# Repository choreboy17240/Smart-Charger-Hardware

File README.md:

# Battery On-Board Charger

## Overview

This repository contains the design files for a Battery On-Board Charger, a DC-DC converter
designed to safely charge sealed lead-acid (SLA) batteries from external power sources. The 
system operates as a buck-boost converter with intelligent microcontroller control for charge
management.

Please see the accompanying software repository on GitHub for an example Arduino STM32 
application that can be built under PlatformIO and used to program the on-board STM32 micro
using an ST-Link programmer.  Programming is done using a custom"SWD-Lite" interface that I 
use for compact, low-cost projects.  SWD-Lite uses a standard 1x4 2.54mm male header to 
provide the absolute minimum number of signals needed or the ST-Link programmer to operate.

I'm sharing this design information and the associated software in hopes that others might 
find it interesting or helpful. It's a hobby project for me, so your mileage may vary!

This is my first attempt to share a KiCad (v9.0) project, so I'd be interested to hear
about whether there are issues or not.  I've exported the global custom symbols and footprints
that I used in the design, so hopefully this should be a standalone PWB design.

## Hardware Specifications

#### Battery Charging
- **Input Voltage**: 12-24V DC
- **Output Voltage**: Adjustable (typically 12V-15.5V for lead-acid batteries)
- **Maximum Charge Current**: 500-600mA
- **Controller**: STM32G030K8T6 (64KB Flash, 8KB RAM)
- **Power Stage**: XL6008 DC-DC converter (Buck-Boost topology)
- **Current Sensing**: INA219 I2C sensor
- **Voltage Control**: MCP4726A0 I2C DAC
- **Status Indicator**: RGB LED
- **Interfaces**: UART, I2C, SWD programming port
- **Operating Temperature**: Room temp

#### Battery Undervoltage Protection 
- **Low-Voltage Cutout**: Adjustable limit (trim pot)

## Key Features

- Software-adjustable charge voltage via I2C DAC
- Real-time current and voltage monitoring
- Temperature-compensated charging profiles
- Multi-stage charging (bulk, absorption, float)
- Status indication via RGB LED
- UART interface for diagnostics and monitoring
- Surge and reverse polarity protection
- Thermal management and over-current protection

## Power Conversion Design

The design utilizes an XL6008 DC-DC converter configured in a buck-boost topology:
- Input filtering through hybrid aluminum capacitors
- High-efficiency power inductors (47µH Sunlord MWSA1004S)
- Schottky diode rectification (B360AE)
- High-quality output filtering with polymer capacitors
- Feedback network with DAC-controlled reference voltage

## PCB Design Considerations

- 2-layer PCB with optimized (kinda) thermal design
- Ground plane for noise reduction and thermal dissipation
- Separate analog and digital ground regions
- Thermal management for XL6008 regulator
- EMI/EMC design practices for switching converter
- Power and signal path optimization

## Undervoltage Protection Circuit

The design incorporates a hardware-based undervoltage protection circuit
to prevent battery damage while under load:

- **Components**:
  - LM339 Quad Comparator for voltage threshold detection
  - MMBT3906 PNP transistor (Q1) for relay driver
  - NS_SRS_SPDT relay (K1) for power disconnection
  - Precision resistor divider network for voltage sensing

- **Operation**:
  - Continuously monitors the battery voltage through a resistive divider
  - When battery voltage falls below a preset threshold (adjustable via the
    RV1 trim pot)
  - Comparator triggers, driving the PNP transistor into conduction
  - Relay energizes, disconnecting the load from the battery
  - Hysteresis provided by R11 (1MΩ) prevents oscillation at threshold
  - D4 provides flyback protection for relay coil

- **Benefits**:
  - Prevents deep discharge of batteries
  - Hardware-based protection operates independently of microcontroller
  - Adjustable threshold for different battery types
  - Fast response time for critical undervoltage conditions
  - Failsafe design ensures load disconnection on power loss

The circuit provides essential protection for battery-powered systems, preventing
damage from excessive discharge while allowing normal operation above the safe 
voltage threshold.

**Note:** As battery voltage limits vary across manufacturers and also depend
on how aggressive you want to be in draining the battery, you will need to 
adjust the RV1 trim potentiometer so that the shutoff occurs at the desired 
voltage. Typical range might be around 11.0-11.5 volts, but check the manufacturer's
recommendation for your battery!

## Thermal Performance

The design has been thermally optimized for enclosed operation:
- Maximum regulator temperature: ~52°C (125°F) at 600mA continuous charging
- Thermal steady state reached after ~30 minutes of operation
- Heat-generating components spaced for optimal thermal dissipation
- Current limited to 600mA for reliability in enclosed environments
- Charging current is constrained by the small heat sink are available for the 
  XL6008 converter, driven by the small packaging space availabe in my project.
- Control software limits the maximum current to that range automatically, but
  this is configurable.
- Redesign the PWB to increase the heat sink area or add a glue-on heat sink
  to the XL6008 if you want higher charging current.

## Usage Notes

See the system connection diagram in the `System` folder for details on how
to connect the module for charging and powering a load from the SLA battery.
The DPDT center-off switch allows the user to select between the following
operating modes:
1. `Charge`: Standby mode with the load off and battery being charged
2. `Power`: Active mode with the load on and charger disconnected
3. `Off`: Shuts down the system completely (no charging, no power to load)

The system should nomrally be left in the `Charge` mode, as the smart charger
is designed to charge up the battery and then automatically shift to a 
standby mode for a software configurable period (default is one week) to 
avoid overcharging the battery.

Charging the battery:
1. Switch the DPDT switch to the `Charge`position
2. The charger automatically determines charge state and applies appropriate charging profile
3. RGB LED color and flashing rate indicates charging status:
   - Blue (fast): Fast bulk charging
   - Yellow (medium): Absorption charging
   - Green (slow): Float/maintenance charging
   - Green (short keep-alive pulse every second): Standby mode
4. Once the battery is charged sufficiently, the charger will enter the standby
   state until it's time to top-off the battery.
   
Using the battery to power a load:
1. Switch the DPDT switch to the `Power` position
2. Battery protection circuit will automatically shut-off the load if battery
   voltage drops below the adjustable threshold.

## Software Configuration

The STM32G030 microcontroller requires appropriate firmware to control the charging process:
- Voltage setpoint control via MCP4726A0 DAC
- Current and voltage monitoring via INA219
- Temperature compensation
- Charging state machine
- Safety monitoring

See the companion firmware repository for microcontroller code.

## Limitations

- Maximum continuous charging current limited to 600mA for thermal management
- Not suitable for high-current applications without additional cooling
- Designed for lead-acid batteries (AGM, Gel, Flooded)
- Requires appropriate firmware for operation

## License

MIT open-source license - see the LICENSE file for details.

## Revision History

- 1.0: Initial design released to JLCPCB for prototype boards
- 1.1: Minor updates for silkscreen fixes

## Contact

Email: choreboy17240@gmail.com

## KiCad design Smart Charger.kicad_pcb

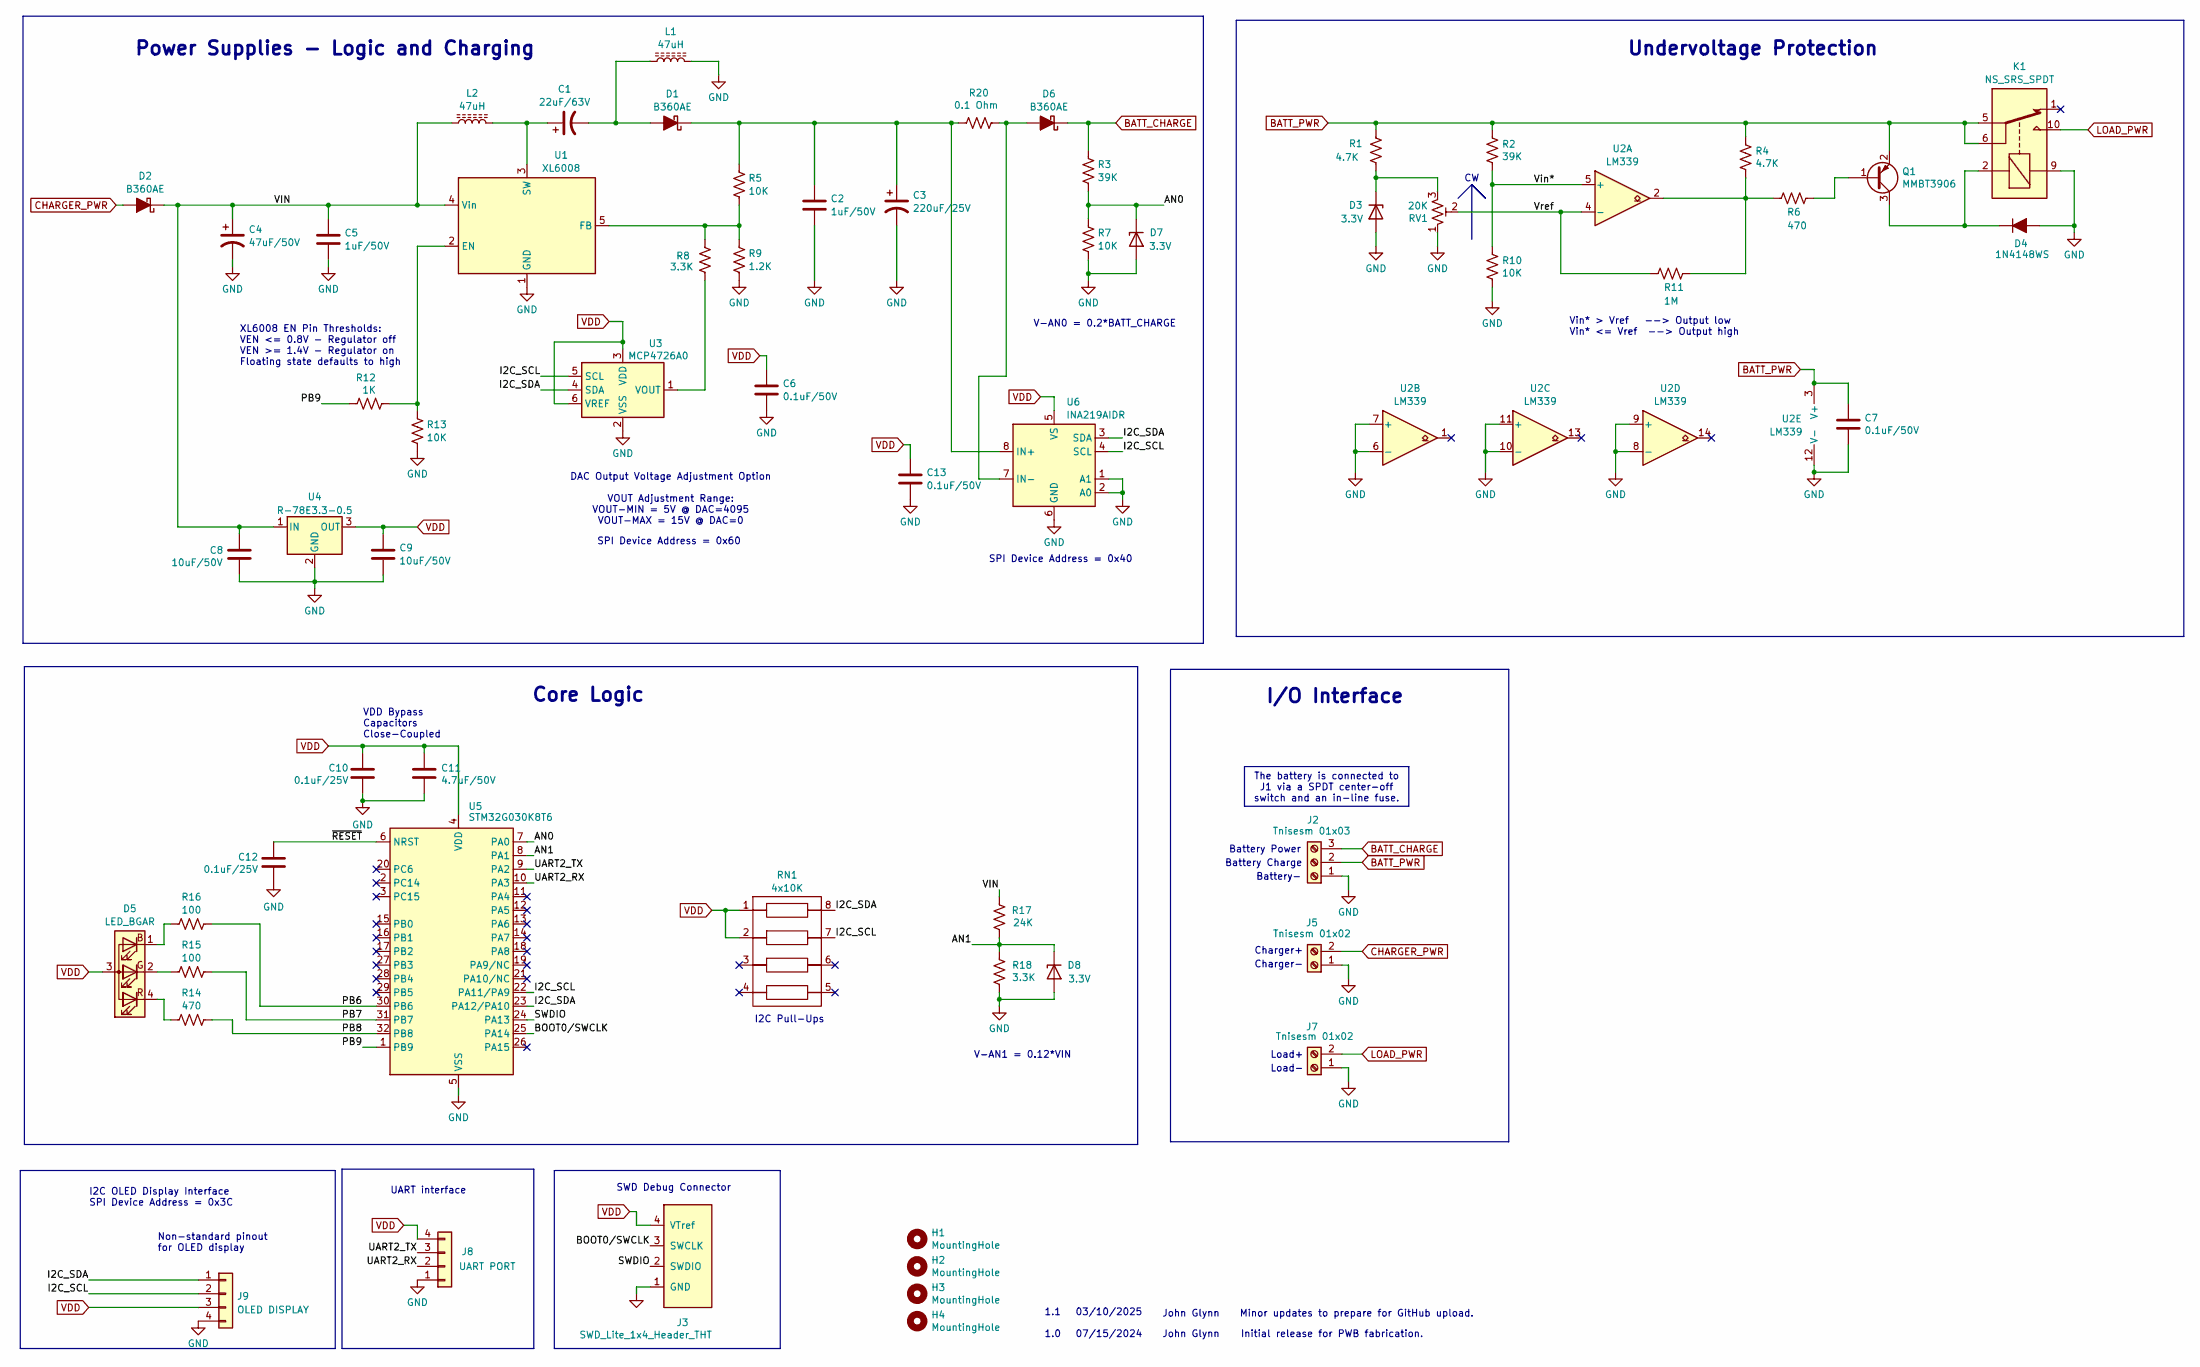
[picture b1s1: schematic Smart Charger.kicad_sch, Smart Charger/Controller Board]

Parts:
C1: 22uF/63V; CP_Elec_6.3x7.7; Mfr P/N HHXB630ARA220MF80G
C2, C5: 1uF/50V; C_1206_3216Metric_Pad1.33x1.80mm_HandSolder; Mfr P/N CL31A105KB9LNNC
C3: 220uF/25V; CP_Radial_D8.0mm_P3.50mm; Mfr P/N APSG250ELL221MHB5S
C4: 47uF/50V; CP_Elec_6.3x7.7; Mfr P/N UUD1H470MCL1GS
C6, C7, C13: 0.1uF/50V; C_0805_2012Metric_Pad1.18x1.45mm_HandSolder; Mfr P/N CC0805KRX7R9BB104
C8, C9: 10uF/50V; C_1206_3216Metric_Pad1.33x1.80mm_HandSolder; Mfr P/N CL31B106KBHNNNE
C10, C12: 0.1uF/25V; C_1206_3216Metric_Pad1.33x1.80mm_HandSolder; Mfr P/N CC1206KRX7R8BB104
C11: 4.7uF/50V; C_1206_3216Metric_Pad1.33x1.80mm_HandSolder; Mfr P/N CL31B475KBHNNNE
D1, D2, D6: B360AE; D_SMA_Handsoldering; Mfr P/N B360AE-13
D3, D7, D8: 3.3V; D_1206_3216Metric_Pad1.42x1.75mm_HandSolder; Mfr P/N MMSZ5226BT1G
D4: 1N4148WS; D_SOD-323_HandSoldering; Mfr P/N 1N4148WS
D5: LED_BGAR; LED_D5.0mm-4_RGB_Staggered_Pins; Mfr P/N N/A
H1, H2, H3, H4: MountingHole; MountingHole_#4-40_Screw
J2: Tnisesm 01x03; TerminalBlock_Tnisesm_Screw_1x03_P5.00mm
J3: SWD_Lite_1x4_Header_THT; PinHeader_1x04_P2.54mm_Vertical
J5, J7: Tnisesm 01x02; TerminalBlock_Tnisesm_Screw_1x02_P5.00mm
J8: UART PORT; PinHeader_1x04_P2.54mm_Vertical
J9: OLED DISPLAY; PinSocket_1x04_P2.54mm_Vertical; Mfr P/N PM254-1-04-Z-8.5
K1: NS_SRS_SPDT; Relay_SPDT_Songle_Miniature_SRS; Mfr P/N SRS-xxVDC-SL
L1, L2: 47uH; L_SMD_Sunlord_MWSA1004S_10.0x11.5mm; Mfr P/N MWSA1004S-470MT
Q1: MMBT3906; SOT-23_Handsolder_Large_Pads; Mfr P/N MMBT3904_R1_00001
R1, R4: 4.7K; R_1206_3216Metric_Pad1.30x1.75mm_HandSolder; Mfr P/N TBD
R2, R3: 39K; R_1206_3216Metric_Pad1.30x1.75mm_HandSolder; Mfr P/N TBD
R5, R7, R10, R13: 10K; R_1206_3216Metric_Pad1.30x1.75mm_HandSolder; Mfr P/N TBD
R6, R14: 470; R_1206_3216Metric_Pad1.30x1.75mm_HandSolder; Mfr P/N TBD
R8, R18: 3.3K; R_1206_3216Metric_Pad1.30x1.75mm_HandSolder; Mfr P/N TBD
R9: 1.2K; R_1206_3216Metric_Pad1.30x1.75mm_HandSolder; Mfr P/N TBD
R11: 1M; R_1206_3216Metric_Pad1.30x1.75mm_HandSolder; Mfr P/N TBD
R12: 1K; R_1206_3216Metric_Pad1.30x1.75mm_HandSolder; Mfr P/N TBD
R15, R16: 100; R_1206_3216Metric_Pad1.30x1.75mm_HandSolder; Mfr P/N TBD
R17: 24K; R_1206_3216Metric_Pad1.30x1.75mm_HandSolder; Mfr P/N TBD
R20: 0.1 Ohm; R_1210_3225Metric_Pad1.30x2.65mm_HandSolder; Mfr P/N TBD
RN1: 4x10K; RN_Array_4x0603; Mfr P/N YC164-FR-0710KL
RV1: 20K; Potentiometer_Bourns_3362P_Vertical; Mfr P/N 3362P-1-223LF
U1: XL6008; TO-252-5L_TabPin3_Hand_Solder; Mfr P/N XL6008E1
U2: LM339; SOIC-14_3.9x8.7mm_P1.27mm; Mfr P/N LM339DR2G
U3: MCP4726A0; SOT-23-6; Mfr P/N MCP4726A0T-E/CH
U4: R-78E3.3-0.5; Converter_DCDC_RECOM_R-78E-0.5_THT
U5: STM32G030K8T6; LQFP-32_7x7mm_P0.8mm; Mfr P/N STM32G030K8T6
U6: INA219AIDR; SOIC-8_3.9x4.9mm_P1.27mm; Mfr P/N INA219AIDR

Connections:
/AN0: D7.1 (K), R3.2, R7.1, U5.7 (PA0)
/AN1: D8.1 (K), R17.2, R18.1, U5.8 (PA1)
/BOOT0/SWCLK: J3.3 (SWCLK), U5.25 (PA14)
/I2C_SCL: J9.2, RN1.7 (R2B), U3.5 (SCL), U5.22 (PA11/PA9), U6.4 (SCL)
/I2C_SDA: J9.1, RN1.8 (R1B), U3.4 (SDA), U5.23 (PA12/PA10), U6.3 (SDA)
/PB6: R16.1, U5.30 (PB6)
/PB7: R15.1, U5.31 (PB7)
/PB8: R14.1, U5.32 (PB8)
/PB9: R12.2, U5.1 (PB9)
/SWDIO: J3.2 (SWDIO), U5.24 (PA13)
/UART2_RX: J8.2, U5.10 (PA3)
/UART2_TX: J8.3, U5.9 (PA2)
/VIN: C4.1, C5.2, C8.1, D2.1 (K), L2.1, R17.1, U1.4 (Vin), U4.1 (IN)
/Vin*: R2.2, R10.1, U2.5 (+)
/Vref: R11.2, RV1.2, U2.4 (-)
/~RESET: C12.1, U5.6 (NRST)
BATT_CHARGE: D6.1 (K), J2.3, R3.1
BATT_PWR: C7.1, J2.2, K1.5, K1.6, Q1.2 (E), R1.1, R2.1, R4.1, U2.3 (V+)
CHARGER_PWR: D2.2 (A), J5.2
GND: C2.1, C3.2, C4.2, C5.1, C6.2, C7.2, C8.2, C9.2, C10.2, C11.2, C12.2, C13.2, D3.2 (A), D4.2 (A), D7.2 (A), D8.2 (A), J2.1, J3.1 (GND), J5.1, J7.1, J8.1, J9.4, K1.9, L1.2, R7.2, R9.2, R10.2, R13.2, R18.2, RV1.1, U1.1 (GND), U2.6 (-), U2.7 (+), U2.8 (-), U2.9 (+), U2.10 (-), U2.11 (+), U2.12 (V-), U3.2 (VSS), U4.2 (GND), U5.5 (VSS), U6.1 (A1), U6.2 (A0), U6.6 (GND)
LOAD_PWR: J7.2, K1.10
unnamed: C1.2, D1.2 (A), L1.1
unnamed: C2.2, C3.1, D1.1 (K), R5.1, R20.2, U6.8 (IN+)
unnamed: D3.1 (K), R1.2, RV1.3
unnamed: D4.1 (K), K1.2, Q1.3 (C)
unnamed: D5.1 (BK), R16.2
unnamed: D5.2 (GK), R15.2
unnamed: D5.4 (RK), R14.2
unnamed: D6.2 (A), R20.1, U6.7 (IN-)
unnamed: Q1.1 (B), R6.1
unnamed: R4.2, R6.2, R11.1, U2.2
unnamed: R12.1, R13.1, U1.2 (EN)
unnamed: R5.2, R8.2, R9.1, U1.5 (FB)
unnamed: C1.1, L2.2, U1.3 (SW)
unnamed: R8.1, U3.1 (VOUT)
VDD: C6.1, C9.1, C10.1, C11.1, C13.1, D5.3 (A), J3.4 (VTref), J8.4, J9.3, RN1.1 (R1A), RN1.2 (R2A), U3.3 (VDD), U3.6 (VREF), U4.3 (OUT), U5.4 (VDD), U6.5 (VS)

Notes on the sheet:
Battery Charge
Battery-
I/O Interface
DAC Output Voltage Adjustment Option VOUT Adjustment Range: VOUT-MIN = 5V @ DAC=4095 VOUT-MAX = 15V @ DAC=0
Battery Power
I2C Pull-Ups
VDD Bypass Capacitors Close-Coupled
Initial release for PWB fabrication.
Minor updates to prepare for GitHub upload.
Charger+
1.0
Power Supplies - Logic and Charging
Non-standard pinout for OLED display
I2C OLED Display Interface SPI Device Address = 0x3C
Load+
SPI Device Address = 0x60
John Glynn
Vin* > Vref --> Output low Vin* <= Vref --> Output high
XL6008 EN Pin Thresholds: VEN <= 0.8V - Regulator off VEN >= 1.4V - Regulator on Floating state defaults to high
03/10/2025
Load-
V-AN1 = 0.12*VIN
UART interface
V-AN0 = 0.2*BATT_CHARGE
Undervoltage Protection
Core Logic
1.1
07/15/2024
Charger-
SPI Device Address = 0x40
SWD Debug Connector
The battery is connected to J1 via a SPDT center-off switch and an in-line fuse.

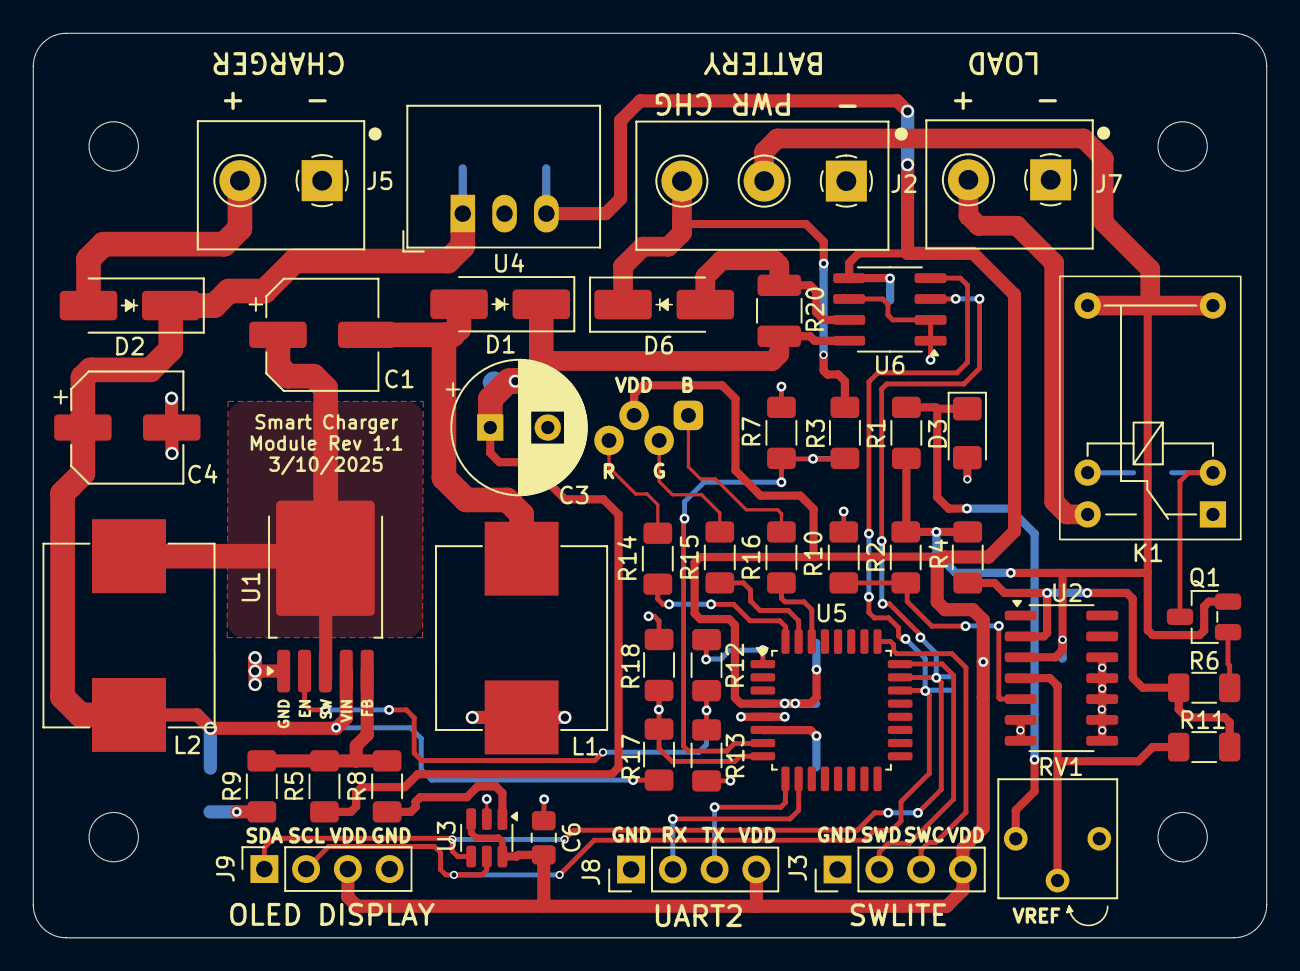
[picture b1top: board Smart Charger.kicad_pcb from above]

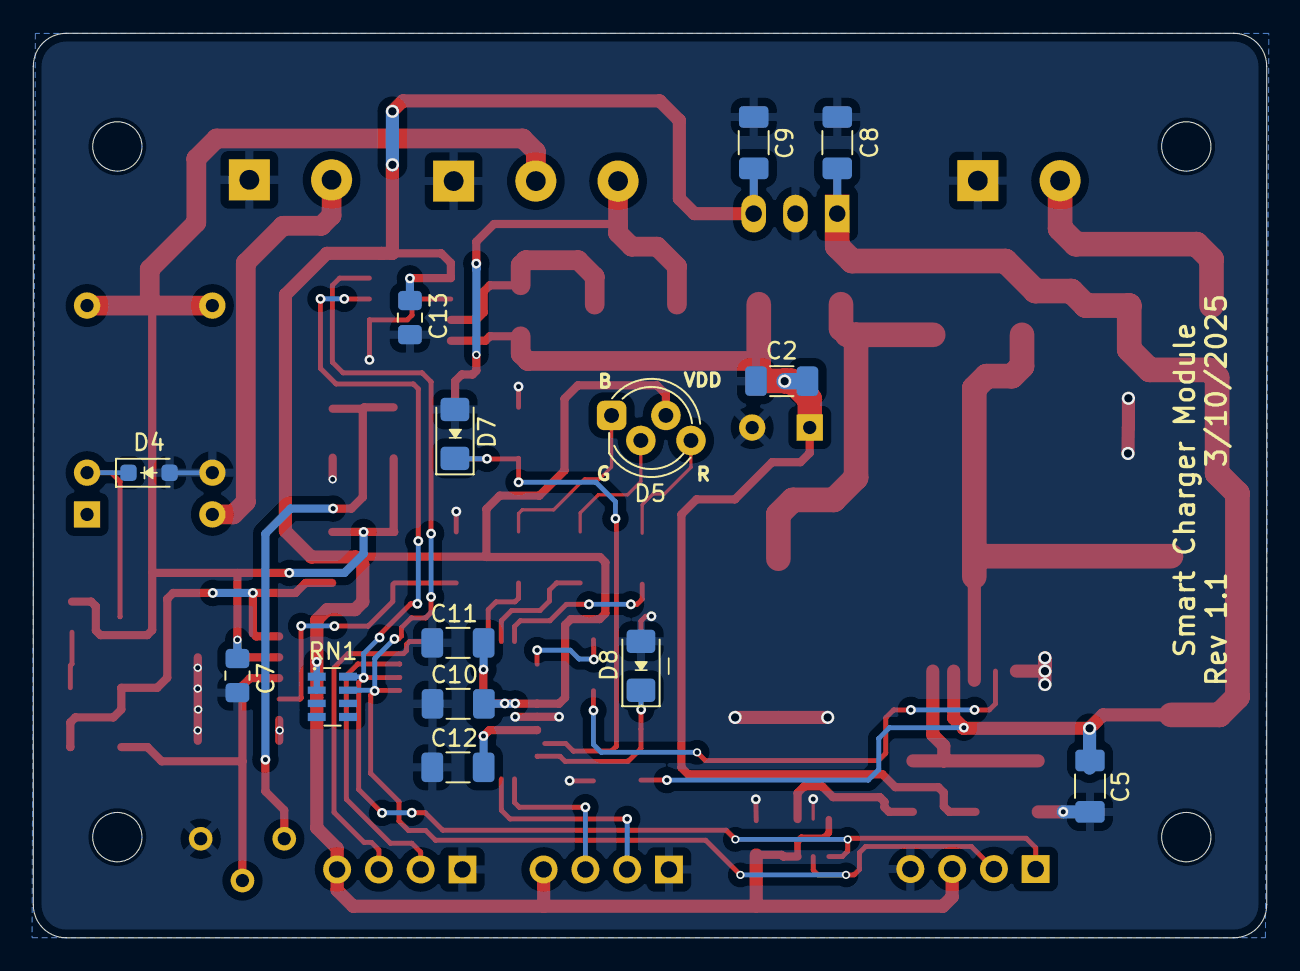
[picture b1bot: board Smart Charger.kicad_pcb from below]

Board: 2 copper layers, 75.0 x 55.0 mm, 62 parts (14 on the bottom side), 36 nets.

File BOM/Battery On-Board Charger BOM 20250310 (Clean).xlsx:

Battery On-Board Charger Project |  |  |  |  |  |  |  | Revision: 03/10/2025
Reference | Qty | Value | Supplier | Supplier P/N | Manufacturer | Mfr P/N | Description | Comments
C1 | 1 | 22uF/63V | LCSC | C7472372 | NCC | HHXB630ARA220MF80G | Hybrid Al Capacitor SMD D6.3xL7.7mm 22uF 63V 1.5A@100kHz | N/A
C2,C5 | 2 | 1uF/50V | LCSC | C444884 | Samsung | CL31A105KB9LNNC | MLCC Capacitor SMD 1206 1uF 50V X5R | Also available from Digikey
C3 | 1 | 220uF/25V | LCSC | C133440 | NCC | APSG250ELL221MHB5S | Solid Al Capacitor Radial D8xP3.5xL11.5mm 220uF 25V 4.65A@100kHz | N/A
C4 | 1 | 47uF/50V | LCSC | C445256 | Nichicon | UUD1H470MCL1GS | Al Electrolytic Capacitor SMD D6.3xL7.7mm 47uF 50V 230mA@10kHz | N/A
C6,C7,C13 | 3 | 0.1uF/50V | LCSC | C49678 | Yageo | CC0805KRX7R9BB104 | MLCC Capacitor SMD 0805 0.1uF 50V X7R
C8,C9 | 2 | 10uF/50V | LCSC | C89632 | Samsung | CL31B106KBHNNNE | MLCC Capacitor SMD 1206 10uF 50V X7R | Replaces X5R version CL31A106MBHNNNE, also available from Digikey
C10,C12 | 2 | 0.1uF/25V | LCSC | C527347 | Yageo | CC1206KRX7R8BB104 | MLCC Capacitor SMD 1206 0.1uF 25V X7R
C11 | 1 | 4.7uF/50V | LCSC | C51205 | Samsung | CL31B475KBHNNNE | MLCC Capacitor SMD 1206 4.7uF 50V X7R | Also available from Digikey
D1,D2,D6 | 3 | B360AE | LCSC | C412514 | Diodes Inc | B360AE-13 | Schottky Diode SMD SMA 3A 60V Low-Leakage | N/A
D3,D7,D8 | 3 | 3.3V | LCSC | C235771 | On Semi | MMSZ5226BT1G | Diode Zener 3.3V 500mw SOD123
D4 | 1 | 1N4148WS | LCSC | Multiple | Multiple | 1N4148WS | Diode SMD SOD-323 300mA 75V | N/A
D5 | 1 | LED_BGAR | Amazon | N/A | Chanzon | N/A | Chanzon RGB LED THT 5mm BGAR | N/A
J2 | 1 | Tnisesm 01x03 | Stock | N/A | Tnisesm |  | Tnisesm Terminal Block P5mm 1x3 | Amazon
J3 | 1 | SWD_Lite_1x4_Header_THT | Stock |  |  |  | Header Male THT P2.54 1x4P
J5,J7 | 2 | Tnisesm 01x02 | Stock | N/A | Tnisesm |  | Tnisesm Terminal Block P5mm 1x2 | Amazon
J8 | 1 | UART PORT | Stock |  |  |  | Header Male THT P2.54 1x4P
J9 | 1 | OLED DISPLAY | LCSC | C2897367 | HCTL | PM254-1-04-Z-8.5 | Header Female THT P2.54 1x4P
K1 | 1 | NS_SRS_SPDT | LCSC | C32429 | Ningbo Songle | SRS-12VDC-SL | Ningbo Songle Miniature PCB Relay SRS, SPDT, 3A | DIP-12 footprint
L1,L2 | 2 | 47uH | LCSC | C408491 | Sunlord | MWSA1004S-470MT | Power Inductor 47uH 2.8A 147mOhm 10.0x11.5mm SMD | N/A
Q1 | 1 | MMBT3906 | DigiKey |  | Panjit International | MMBT3904_R1_00001 | TRANS PNP 45V 0.8A SOT23
R1,R4 | 2 | 4.7K | Stock |  | Various | TBD | Resistor SMD 1206 | N/A
R2,R3 | 2 | 39K | Stock |  | Various | TBD | Resistor SMD 1206 | N/A
R5,R7,R10,R13 | 4 | 10K | Stock |  | Various | TBD | Resistor SMD 1206 | N/A
R6 | 1 | 470 | Stock |  | Various | TBD | Resistor SMD 1206 | N/A
R8 | 1 | 2.9K | Stock |  | Various | TBD | Resistor SMD 1206 | N/A
R9 | 1 | 1.2K | Stock |  | Various | TBD | Resistor SMD 1206 | N/A
R11 | 1 | 1M | Stock |  | Various | TBD | Resistor SMD 1206 | N/A
R12 | 1 | 1K | Stock |  | Various | TBD | Resistor SMD 1206 | N/A
R14,R15,R16 | 3 | TBD | Stock |  | Various | TBD | Resistor SMD 1206 | N/A
R17 | 1 | 24K | Stock |  | Various | TBD | Resistor SMD 1206 | N/A
R18 | 1 | 3.3K | Stock |  | Various | TBD | Resistor SMD 1206 | N/A
R20 | 1 | 0.1 Ohm | Stock |  | Various | TBD | Resistor SMD 1206/1210 | N/A
RN1 | 1 | 4x10K | LCSC | C110924 | Yageo | YC164-FR-0710KL | Resistor Array SMD 0603x4 10K Isolated | Compatible with CTS 742C083103JP from Digikey.
RV1 | 1 | 20K | Digikey | 3362P-1-223LF-ND | Bourns | 3362P-1-223LF | Trim potentiometer, 22K, 1-turn | "P" footprint vs "H" footprint
U1 | 1 | XL6008 | LCSC | C73012 | XLSEMI | XL6008E1 | 60V 3A Switching Current Boost/Buck_Boost/Inverting DC/DC Converter | N/A
U2 | 1 | LM339 | LCSC | C63821 | On Semi | LM339DR2G | LM339 Quad Comparator SMD SOIC-14
U3 | 1 | MCP4726A0 | LCSC | C191581 | Microchip | MCP4726A0T-E/CH | MCP4726A0 DAC 12-bit I2C interface EEPROM SMD SOT-23-6 | Also available at Digikey
U4 | 1 | R-78E3.3-0.5 | Stock |  |  |  | R-78E3.3-0.5 DC DC Converter 3.3V 2W | RECOM or equivalent
U5 | 1 | STM32G030K8T6 | LCSC | C431631 | ST Micro | STM32G030K8T6 | STM32G030K8T6 64KB Flash 8KB Ram LQFP-32 MCU
U6 | 1 | INA219AIDR | LCSC | C138706 | TI | INA219AIDR | INA219A Current/Power Sensor with I2C SMD SOIC-8

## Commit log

2025-03-10 v1.1 release for upload to GitHub
2025-03-10 Added README and license information.
2025-03-11 Added system connection drawing and updated README.md file with system information.
